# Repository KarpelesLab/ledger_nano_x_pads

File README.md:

# Ledger Nano X board map

An interactive map of the Ledger Nano X main board: its 40 test pads, the copper traces between them and the
chips, and a KiCad reconstruction of the whole board.

**View it online: https://karpeleslab.github.io/ledger_nano_x_pads/**

- [Photo viewer](https://karpeleslab.github.io/ledger_nano_x_pads/flip.html): photos of both sides, with and
  without components, overlaid with every traced net, test pad and part; hover anything for details.
- [3D viewer](https://karpeleslab.github.io/ledger_nano_x_pads/kicad/viewer3d.html): the KiCad reconstruction
  with every part and its marking; hover a track, pad or chip to light up its net.

This is a reconstruction from photos, not the manufacturer's design: inner layers are assumed, footprints are
approximate, and names ending in "?" are likely but not confirmed.

## Test pads

The 40 numbered test pads on the back of the board, as labelled in the photos. Names ending in "?" are likely but
not confirmed; the others were measured or follow from what the pad connects to.

<!-- test-pads:start -->
| Pad | Signal | Notes |
|---|---|---|
| 01 | USB CC2 |  |
| 02 | Left button power | Lets the left button also act as the power button; exact role not yet known |
| 03 | *not identified* |  |
| 04 | MCU PB7 | MCU PB7 through R30; role not known |
| 05 | PD SCL | STUSB4500L pin 7, I2C clock (not to the MCU, likely for configuration), as TP09 is its SDA |
| 06 | BAT NTC | The battery's temperature sensor (NTC): battery pad 1, and through R1 the charger's TH pin (PWR1 pin 8) |
| 07 | Charger input? | Input supply of the L6924D charger (PWR1 pins 1, 2), fed from VBUS by the X12 power switch, also the anode of the X9 Zener; R31 feeds it to the MCU PA1 voltage sense; not measured |
| 08 | *not identified* |  |
| 09 | PD SDA | STUSB4500L pin 8, I2C data (not to the MCU, likely for configuration), as TP05 is its SCL |
| 10 | I2C1 SCL |  |
| 11 | PD VBUS_EN_SNK |  |
| 12 | VBUS |  |
| 13 | Charger VREF | 1.8 V reference of the L6924D charger (PWR1 pin 12), decoupled by C37 |
| 14 | VBAT | Battery +: battery pad 3, the charger's battery sense (PWR1 VOSNS, pin 10), the fuel gauge (PWR2 pin 9) and X9's unconnected pin |
| 15 | Charger ST2 | Status output ST2 of the L6924D charger (PWR1 pin 3) to MCU PA2, a wake-up input |
| 16 | MCU PB3 | MCU PB3 through R16, with R28 and R29 (to TP07's net); role not known |
| 17 | I2C1 SDA |  |
| 18 | Charger IPRG | Charge current program pin of the L6924D charger (PWR1 pin 15), with R14 to ground |
| 19 | Left button power | Lets the left button also act as the power button; exact role not yet known |
| 20 | SWCLK | Legacy SWD debug access: Ledger originally left the STM32 unlocked so users could verify the device's state over SWD. That was shown to be a risk, and the STM32 now ships locked, so this port can no longer be used |
| 21 | SWDIO | Legacy SWD debug access: Ledger originally left the STM32 unlocked so users could verify the device's state over SWD. That was shown to be a risk, and the STM32 now ships locked, so this port can no longer be used |
| 22 | Supply sense (MCU PA1) | Voltage sense into MCU PA1 (ADC1_IN6): R31 and R32 divide down the supply on TP07's net, R32 to ground |
| 23 | GND |  |
| 24 | +3.3V rail |  |
| 25 | MCU PA5 | MCU PA5, with R19 and R37; role not known |
| 26 | MCU NRST |  |
| 27 | Charger SD | MCU PA7 (pin 16), joined on an inner layer to the shutdown pin (SD, pin 7) of the L6924D charger, which R11 holds low to enable it: PA7 can likely switch charging off |
| 28 | Left button |  |
| 29 | SE RESET |  |
| 30 | SE CLK-IN |  |
| 31 | OLED SPI CS |  |
| 32 | SEPROXYHAL |  |
| 33 | OLED RESET? | Likely OLED reset, not confirmed: goes to the main MCU, not the secure element |
| 34 | OLED CLK |  |
| 35 | OLED MOSI |  |
| 36 | OLED D/C |  |
| 37 | OLED VCOMH? | BTB pin 9, filtered by C31 to ground: likely the OLED controller's VCOMH, which only needs a capacitor; not measured |
| 38 | OLED VCC | The OLED panel supply (7.5 to 16.5 V for an SSD1312): output of the X10 TLV61046A boost converter, to BTB pin 12; voltage not measured |
| 39 | OLED IREF? | Likely the OLED controller's IREF, with R33 to ground setting the segment current; not measured |
| 40 | Right button |  |
<!-- test-pads:end -->

## Layout

| Path | Contents |
|---|---|
| `flip.html` | Photo viewer |
| `img/` | Photos of both sides, with and without components, aligned to the same pixel grid; `xray.png`, an X-ray mosaic of the whole board, seen from the back like the photos; `se1_die/`, microscope photos of the decapped secure element die, a 50x overview and four 100x quarters, in the die's own orientation (ST logo top left) |
| `traces.js` | Traced nets: segments per side, vias, ground connection points, names and purposes |
| `pads.js` | The 40 test pads and their signal names |
| `components.js`, `passives.js` | Chips, connectors and other parts; resistors and capacitors |
| `kicad/` | KiCad project generated from the data above, plus the 3D viewer and the scripts that build them |
| `kicad/se1_ct.js` | Model of the secure element from an X-ray CT scan, which the 3D viewer loads when zoomed in on it |
| `kicad/se1_die.jpg` | Photo of the secure element die's top metal layer (the ST K500A die), stitched from the four 100x shots in `img/se1_die/`, cropped to the die edge and turned to match the CT model; the 3D viewer lays it on the die of the CT model |
| `index.html` | Landing page of the published site |

## Working on it

Open `flip.html` in a browser; no server is needed. The traces are edited directly in `traces.js`, one trace
per line with its points in pixel coordinates of the photos. After drawing, `kicad/cleanup_traces.py` then
`kicad/octilinear.py` square the segments to 0/45/90 degrees without changing any connection.

After changing the data, rebuild the KiCad reconstruction and the viewer data (needs KiCad 10 and its Python
module):

```sh
kicad/regenerate.sh   # board, schematic, zone fill, consistency check, overlay.js and scene.js
kicad/render.sh       # optional: 3D renders and a STEP file
```

`regenerate.sh` overwrites `kicad/nanox.kicad_pcb` and `kicad/nanox.kicad_sch`, so edits made in KiCad
itself would be lost.

The site is published by `.github/workflows/pages.yml` on every push to `master`.

## License

Original reverse engineering work by Karpeles Lab Inc., made available for the public good.

- **Code** (the viewers, the scripts under `kicad/` and the workflow): [MIT](LICENSE).
- **Content** (photos, board data, the KiCad project and its 3D models, and this documentation):
  [CC BY 4.0](LICENSE-CC-BY-4.0). Reuse it freely, including commercially, crediting "Karpeles Lab Inc.".

Ledger and Nano X are trademarks of Ledger SAS; this project is not affiliated with or endorsed by Ledger.

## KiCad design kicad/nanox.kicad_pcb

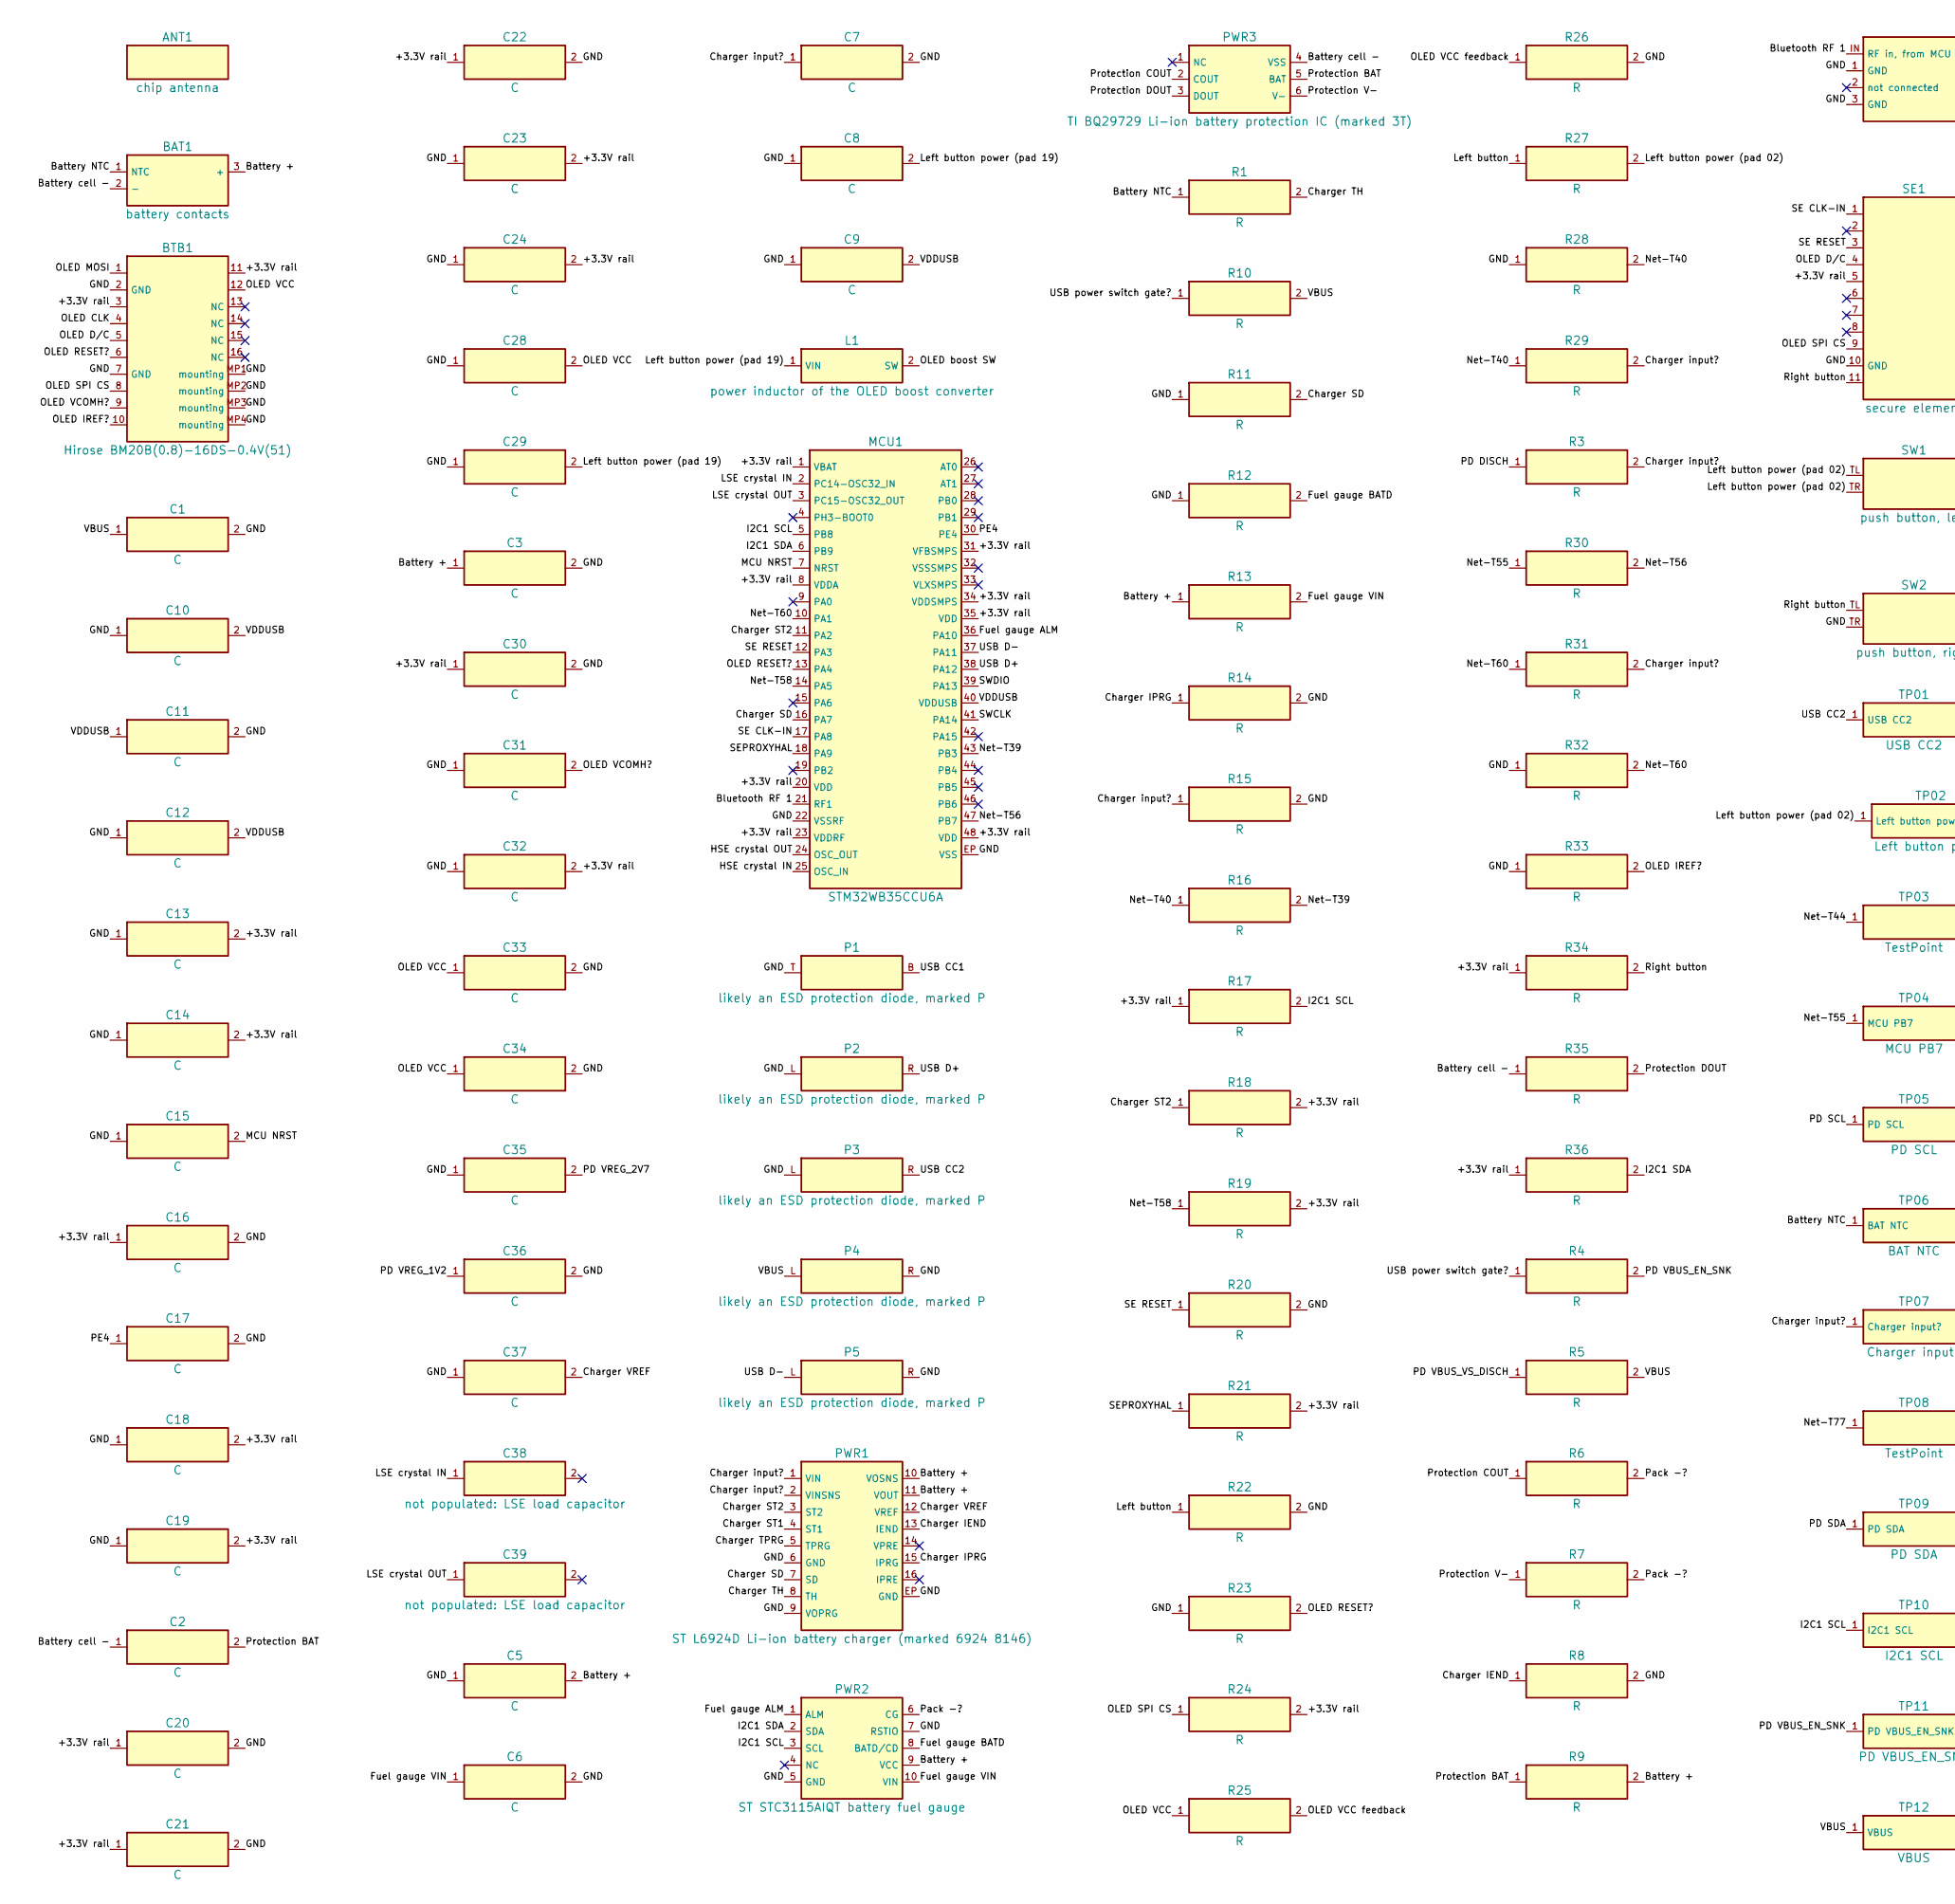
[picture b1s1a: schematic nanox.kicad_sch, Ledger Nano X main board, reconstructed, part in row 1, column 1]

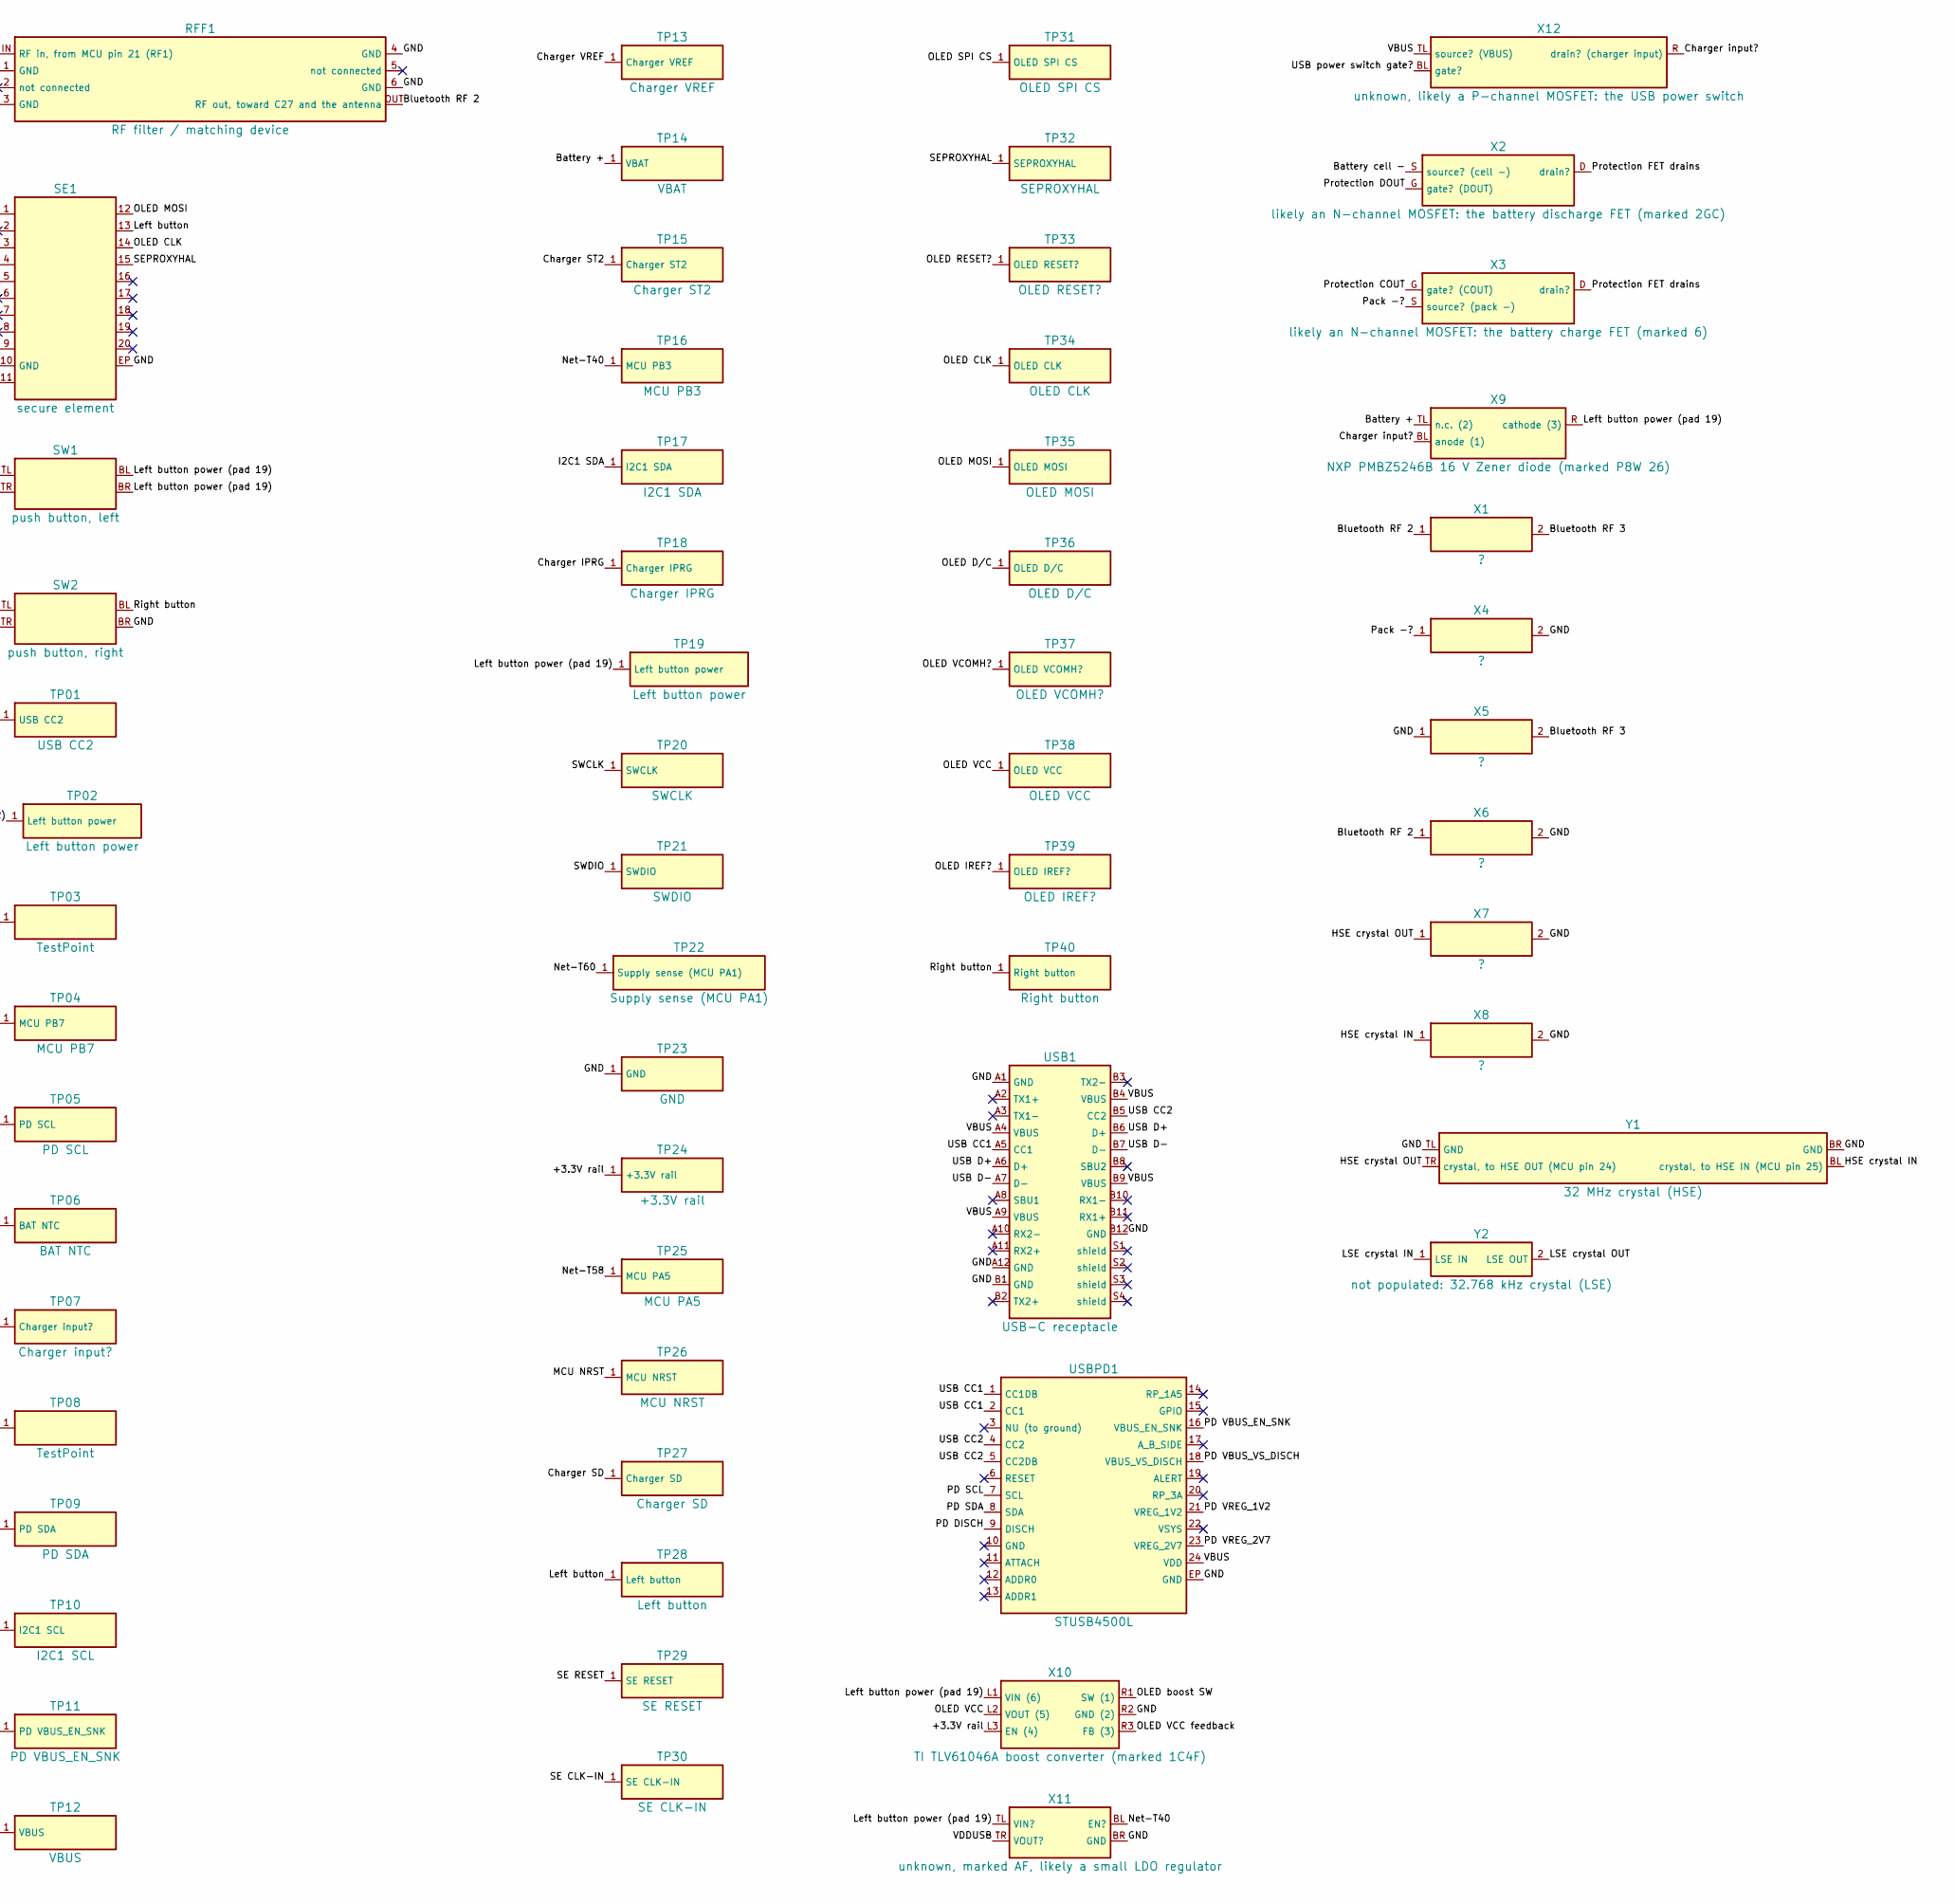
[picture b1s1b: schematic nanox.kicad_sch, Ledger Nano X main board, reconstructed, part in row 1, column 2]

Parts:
ANT1: chip antenna
BAT1: battery contacts
BTB1: Hirose BM20B(0.8)-16DS-0.4V(51)
C1, C2, C3, C5, C6, C7, C8, C9, C10, C11, C12, C13, C14, C15, C16, C17, C18, C19, C20, C21, C22, C23, C24, C28, C29, C30, C31, C32, C33, C34, C35, C36, C37: C
C38, C39: not populated: LSE load capacitor
L1: power inductor of the OLED boost converter
MCU1: STM32WB35CCU6A
P1, P2, P3, P4, P5: likely an ESD protection diode, marked P
PWR1: ST L6924D Li-ion battery charger (marked 6924 814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
PWR2: ST STC3115AIQT battery fuel gauge
PWR3: TI BQ29729 Li-ion battery protection IC (marked 3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
R1, R3, R4, R5, R6, R7, R8, R9, R10, R11, R12, R13, R14, R15, R16, R17, R18, R19, R20, R21, R22, R23, R24, R25, R26, R27, R28, R29, R30, R31, R32, R33, R34, R35, R36: R
RFF1: RF filter / matching device
SE1: secure element
SW1: push button, left
SW2: push button, right
TP01: USB CC2
TP02, TP19: Left button power
TP03, TP08: TestPoint
TP04: MCU PB7
TP05: PD SCL
TP06: BAT NTC
TP07: Charger input?
TP09: PD SDA
TP10: I2C1 SCL
TP11: PD VBUS_EN_SNK
TP12: VBUS
TP13: Charger VREF
TP14: VBAT
TP15: Charger ST2
TP16: MCU PB3
TP17: I2C1 SDA
TP18: Charger IPRG
TP20: SWCLK
TP21: SWDIO
TP22: Supply sense (MCU PA1)
TP23: GND
TP24: +3.3V rail
TP25: MCU PA5
TP26: MCU NRST
TP27: Charger SD
TP28: Left button
TP29: SE RESET
TP30: SE CLK-IN
TP31: OLED SPI CS
TP32: SEPROXYHAL
TP33: OLED RESET?
TP34: OLED CLK
TP35: OLED MOSI
TP36: OLED D/C
TP37: OLED VCOMH?
TP38: OLED VCC
TP39: OLED IREF?
TP40: Right button
USB1: USB-C receptacle
USBPD1: STUSB4500L
X1, X4, X5, X6, X7, X8: ?
X2: likely an N-channel MOSFET: the battery discharge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
X3: likely an N-channel MOSFET: the battery charge FE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
X9: NXP PMBZ5246B 16 V Zener diode (marked P8W 26)
X10: TI TLV61046A boost converter (marked 1C4F)
X11: unknown, marked AF, likely a small LDO regulator
X12: unknown, likely a P-channel MOSFET: the USB power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
Y1: 32 MHz crystal (HSE)
Y2: not populated: 32.768 kHz crystal (LSE)

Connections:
+3.3V rail: BTB1.3, BTB1.11, C13.2, C14.2, C16.1, C18.2, C19.2, C20.1, C21.1, C22.1, C23.2, C24.2, C30.1, C32.2, MCU1.1 (VBAT), MCU1.8 (VDDA), MCU1.20 (VDD), MCU1.23 (VDDRF), MCU1.31 (VFBSMPS), MCU1.34 (VDDSMPS), MCU1.35 (VDD), MCU1.48 (VDD), R17.1, R18.2, R19.2, R21.2, R24.2, R34.1, R36.1, SE1.5, TP24.1, X10.L3 (EN (4))
Battery +: BAT1.3 (+), C3.1, C5.2, PWR1.10 (VOSNS), PWR1.11 (VOUT), PWR2.9 (VCC), R9.2, R13.1, TP14.1, X9.TL (n.c. (2))
Battery NTC: BAT1.1 (NTC), R1.1, TP06.1
Battery cell -: BAT1.2 (-), C2.1, PWR3.4 (VSS), R35.1, X2.S (source? (cell -))
Bluetooth RF 1: MCU1.21 (RF1), RFF1.IN (RF in, from MCU pin 21 (RF1))
Bluetooth RF 2: RFF1.OUT (RF out, toward C27 and the antenna), X1.1, X6.1
Bluetooth RF 3: X1.2, X5.2
Charger IEND: PWR1.13 (IEND), R8.1
Charger IPRG: PWR1.15 (IPRG), R14.1, TP18.1
Charger SD: MCU1.16 (PA7), PWR1.7 (SD), R11.2, TP27.1
Charger ST1: PWR1.4 (ST1)
Charger ST2: MCU1.11 (PA2), PWR1.3 (ST2), R18.1, TP15.1
Charger TH: PWR1.8 (TH), R1.2
Charger TPRG: PWR1.5 (TPRG)
Charger VREF: C37.2, PWR1.12 (VREF), TP13.1
Charger input?: C7.1, PWR1.1 (VIN), PWR1.2 (VINSNS), R3.2, R15.1, R29.2, R31.2, TP07.1, X9.BL (anode (1)), X12.R (drain? (charger input))
Fuel gauge ALM: MCU1.36 (PA10), PWR2.1 (ALM)
Fuel gauge BATD: PWR2.8 (BATD/CD), R12.2
Fuel gauge VIN: C6.1, PWR2.10 (VIN), R13.2
GND: BTB1.2 (GND), BTB1.7 (GND), BTB1.MP1 (mounting), BTB1.MP2 (mounting), BTB1.MP3 (mounting), BTB1.MP4 (mounting), C1.2, C3.2, C5.1, C6.2, C7.2, C8.1, C9.1, C10.1, C11.2, C12.1, C13.1, C14.1, C15.1, C16.2, C17.2, C18.1, C19.1, C20.2, C21.2, C22.2, C23.1, C24.1, C28.1, C29.1, C30.2, C31.1, C32.1, C33.2, C34.2, C35.1, C36.2, C37.1, MCU1.22 (VSSRF), MCU1.EP (VSS), P1.T, P2.L, P3.L, P4.R, P5.R, PWR1.6 (GND), PWR1.9 (VOPRG), PWR1.EP (GND), PWR2.5 (GND), PWR2.7 (RSTIO), R8.2, R11.1, R12.1, R14.2, R15.2, R20.2, R22.2, R23.1, R26.2, R28.1, R32.1, R33.1, RFF1.1 (GND), RFF1.3 (GND), RFF1.4 (GND), RFF1.6 (GND), SE1.10 (GND), SE1.EP, SW2.BR, SW2.TR, TP23.1, USB1.A1 (GND), USB1.A12 (GND), USB1.B1 (GND), USB1.B12 (GND), USBPD1.EP (GND), X4.2, X5.1, X6.2, X7.2, X8.2, X10.R2 (GND (2)), X11.BR (GND), Y1.BR (GND), Y1.TL (GND)
HSE crystal IN: MCU1.25 (OSC_IN), X8.1, Y1.BL (crystal, to HSE IN (MCU pin 25))
HSE crystal OUT: MCU1.24 (OSC_OUT), X7.1, Y1.TR (crystal, to HSE OUT (MCU pin 24))
I2C1 SCL: MCU1.5 (PB8), PWR2.3 (SCL), R17.2, TP10.1
I2C1 SDA: MCU1.6 (PB9), PWR2.2 (SDA), R36.2, TP17.1
LSE crystal IN: C38.1, MCU1.2 (PC14-OSC32_IN), Y2.1 (LSE IN)
LSE crystal OUT: C39.1, MCU1.3 (PC15-OSC32_OUT), Y2.2 (LSE OUT)
Left button: R22.1, R27.1, SE1.13, TP28.1
Left button power (pad 02): R27.2, SW1.TL, SW1.TR, TP02.1
Left button power (pad 19): C8.2, C29.2, L1.1 (VIN), SW1.BL, SW1.BR, TP19.1, X9.R (cathode (3)), X10.L1 (VIN (6)), X11.TL (VIN?)
MCU NRST: C15.2, MCU1.7 (NRST), TP26.1
Net-T39: MCU1.43 (PB3), R16.2
Net-T40: R16.1, R28.2, R29.1, TP16.1, X11.BL (EN?)
Net-T44: TP03.1
Net-T55: R30.1, TP04.1
Net-T56: MCU1.47 (PB7), R30.2
Net-T58: MCU1.14 (PA5), R19.1, TP25.1
Net-T60: MCU1.10 (PA1), R31.1, R32.2, TP22.1
Net-T77: TP08.1
OLED CLK: BTB1.4, SE1.14, TP34.1
OLED D/C: BTB1.5, SE1.4, TP36.1
OLED IREF?: BTB1.10, R33.2, TP39.1
OLED MOSI: BTB1.1, SE1.12, TP35.1
OLED RESET?: BTB1.6, MCU1.13 (PA4), R23.2, TP33.1
OLED SPI CS: BTB1.8, R24.1, SE1.9, TP31.1
OLED VCC: BTB1.12, C28.2, C33.1, C34.1, R25.1, TP38.1, X10.L2 (VOUT (5))
OLED VCC feedback: R25.2, R26.1, X10.R3 (FB (3))
OLED VCOMH?: BTB1.9, C31.2, TP37.1
OLED boost SW: L1.2 (SW), X10.R1 (SW (1))
PD DISCH: R3.1, USBPD1.9 (DISCH)
PD SCL: TP05.1, USBPD1.7 (SCL)
PD SDA: TP09.1, USBPD1.8 (SDA)
PD VBUS_EN_SNK: R4.2, TP11.1, USBPD1.16 (VBUS_EN_SNK)
PD VBUS_VS_DISCH: R5.1, USBPD1.18 (VBUS_VS_DISCH)
PD VREG_1V2: C36.1, USBPD1.21 (VREG_1V2)
PD VREG_2V7: C35.2, USBPD1.23 (VREG_2V7)
PE4: C17.1, MCU1.30 (PE4)
Pack -?: PWR2.6 (CG), R6.2, R7.2, X3.S (source? (pack -)), X4.1
Protection BAT: C2.2, PWR3.5 (BAT), R9.1
Protection COUT: PWR3.2 (COUT), R6.1, X3.G (gate? (COUT))
Protection DOUT: PWR3.3 (DOUT), R35.2, X2.G (gate? (DOUT))
Protection FET drains: X2.D (drain?), X3.D (drain?)
Protection V-: PWR3.6 (V-), R7.1
Right button: R34.2, SE1.11, SW2.BL, SW2.TL, TP40.1
SE CLK-IN: MCU1.17 (PA8), SE1.1, TP30.1
SE RESET: MCU1.12 (PA3), R20.1, SE1.3, TP29.1
SEPROXYHAL: MCU1.18 (PA9), R21.1, SE1.15, TP32.1
SWCLK: MCU1.41 (PA14), TP20.1
SWDIO: MCU1.39 (PA13), TP21.1
USB CC1: P1.B, USB1.A5 (CC1), USBPD1.1 (CC1DB), USBPD1.2 (CC1)
USB CC2: P3.R, TP01.1, USB1.B5 (CC2), USBPD1.4 (CC2), USBPD1.5 (CC2DB)
USB D+: MCU1.38 (PA12), P2.R, USB1.A6 (D+), USB1.B6 (D+)
USB D−: MCU1.37 (PA11), P5.L, USB1.A7 (D-), USB1.B7 (D-)
USB power switch gate?: R4.1, R10.1, X12.BL (gate?)
VBUS: C1.1, P4.L, R5.2, R10.2, TP12.1, USB1.A4 (VBUS), USB1.A9 (VBUS), USB1.B4 (VBUS), USB1.B9 (VBUS), USBPD1.24 (VDD), X12.TL (source? (VBUS))
VDDUSB: C9.2, C10.2, C11.1, C12.2, MCU1.40 (VDDUSB), X11.TR (VOUT?)

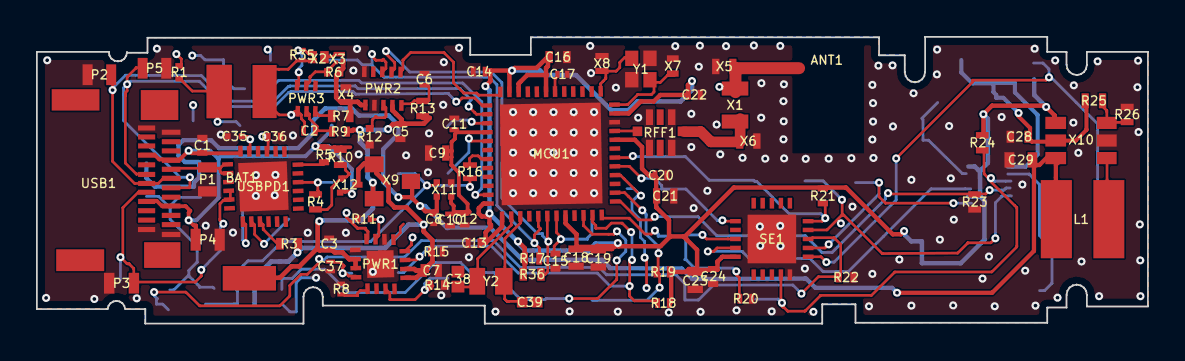
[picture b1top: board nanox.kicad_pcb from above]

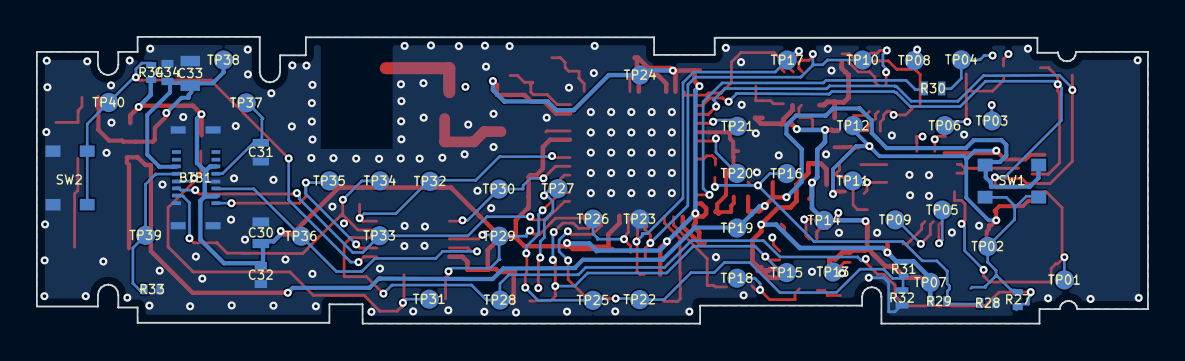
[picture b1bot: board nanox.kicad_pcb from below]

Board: 4 copper layers, 61.7 x 15.9 mm, 143 parts (56 on the bottom side), 71 nets.
